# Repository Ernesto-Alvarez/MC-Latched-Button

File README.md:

# MC-Latched-Button
A button module for activating other high-voltage devices for a specific time

The device uses a microcontroller to control a relay that can be connected to the power supply of mains powered devices.
The button has to be pressed for a preconfigured amount of time (default 5 seconds) and keeps the relay closed for another configurable time (default 12 minutes). Device can be shutdown by pressing the button for a configurable amount of time (default: short press, 0.2 seconds).

Module fits a 2 unit DIN circuit breaker box (but does not attach to rails).

See branch v1 for what works today (not perfectly, but good enough) and branch v2 for what will work in the future (hopefully, perfectly).

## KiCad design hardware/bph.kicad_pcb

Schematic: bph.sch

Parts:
C1: 0.1uF; SM0805
C2: 33uF; EC50
C3: 1uF; SM0805
D1, D2: LED; LED-5mm
D3: DIODE; DO-41
K1: RELAY_SPDT
P1: PGM_UART; SIL-5
P2: AC_PIN; SIL-2
P3: PWR_PIN; SIL-2
P4: AC_TERMINAL; CONN2_175
P5: BUTTON; SIL-2
P6: HV_TERMINAL; CONN2_175
Q1: BC337; TO-92
R1, R2: 330; SM0805
R3: R; SM0805
U1: PIC12F629; DIP-8

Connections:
/HV_TERM_A: K1.3, P6.1
/HV_TERM_B: K1.5, P6.2
/PGC/RXD: P1.5, U1.6 (GP1)
/PGD/TXD: P1.4, U1.7 (GP0)
/RELAY_CTL: R1.1, R3.2, U1.2 (GP5/OSC1)
/VPP: P1.1, U1.4 (GP3/MCLR)
GND: C1.1, C2.2, C3.2, D1.1, D2.1, P1.3, P3.2, P5.2, Q1.3, U1.8 (VSS)
unnamed: D1.2, R1.2
unnamed: D2.2, R2.2
unnamed: D3.2, K1.2, Q1.1
unnamed: P2.1, P4.2
unnamed: P2.2, P4.1
unnamed: P5.1, U1.5 (GP2)
unnamed: Q1.2, R3.1
unnamed: R2.1, U1.3 (GP4/OSC2)
VCC: C1.2, C2.1, C3.1, D3.1, K1.1, P1.2, P3.1, U1.1 (VDD)

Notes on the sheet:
Relay
Microcontroller
Weak pull-up activated on pins 5 and 6
Connectors

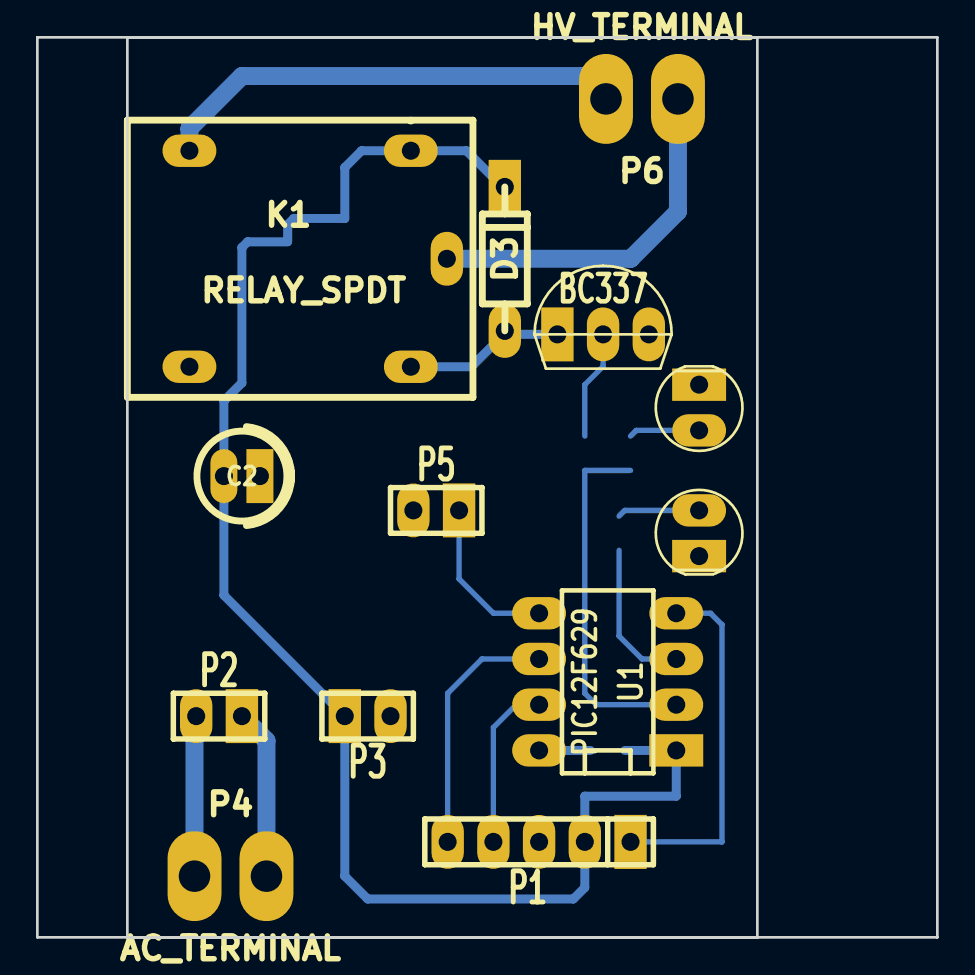
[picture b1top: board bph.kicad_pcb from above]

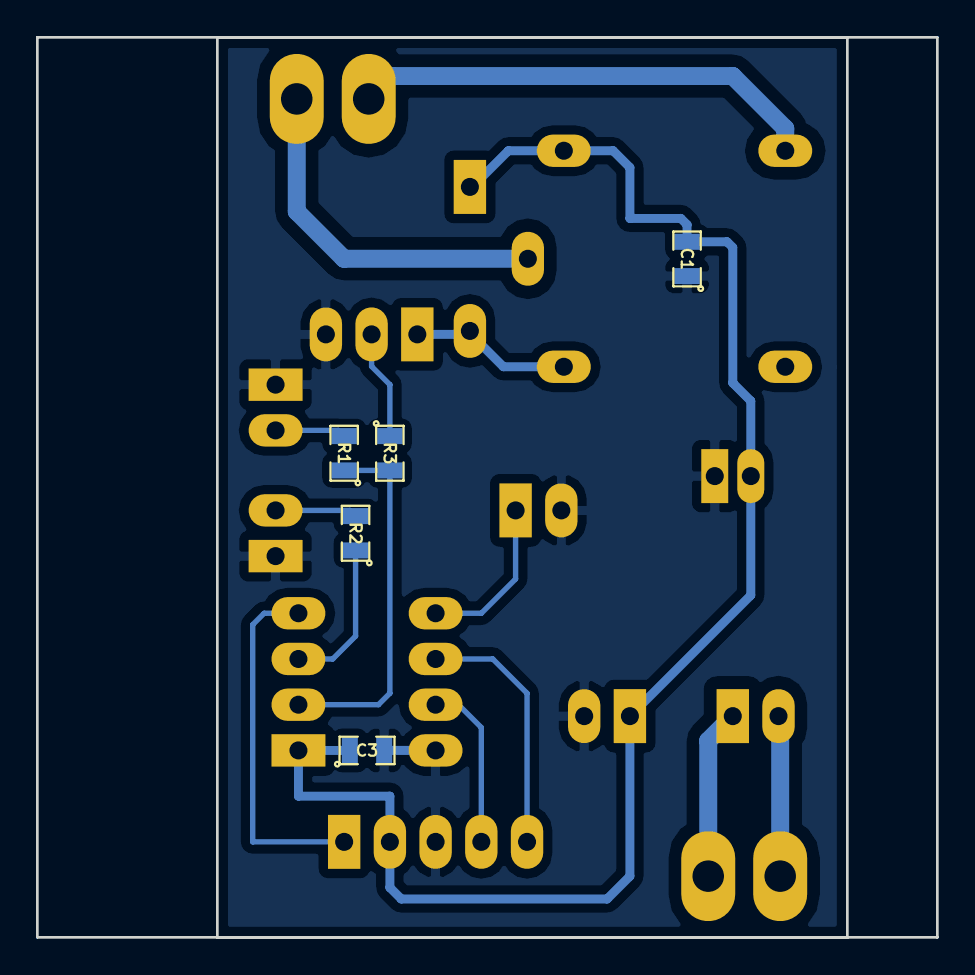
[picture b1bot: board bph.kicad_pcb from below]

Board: 2 copper layers, 50.0 x 50.0 mm, 18 parts (5 on the bottom side), 16 nets.

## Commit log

2018-03-21 The project, as of now.
2018-03-27 Elimination of part of the button-off routine Recreation of the button-push routing to eliminate GOTOs Noting of debouncer bug
2018-03-27 Dropped the faulty debouncer Adjusted the parameters
2018-03-27 The binary file for the latest version
    Now... onward to v2
2018-04-02 manual.txt
    Device manual, first draft. Defined LED state machine.
2018-04-02 Completed the relay state machine
2018-04-04 Prototype LED firmware. Docs to come soon.
2018-04-05 Added explanation of prototype code and set conventions on future code blocks.
2018-07-17 Completed code, loop not yet calibrated
2018-07-18 Loop optimized to under 250 instructions, calibrated to 4000 loops/sec.
